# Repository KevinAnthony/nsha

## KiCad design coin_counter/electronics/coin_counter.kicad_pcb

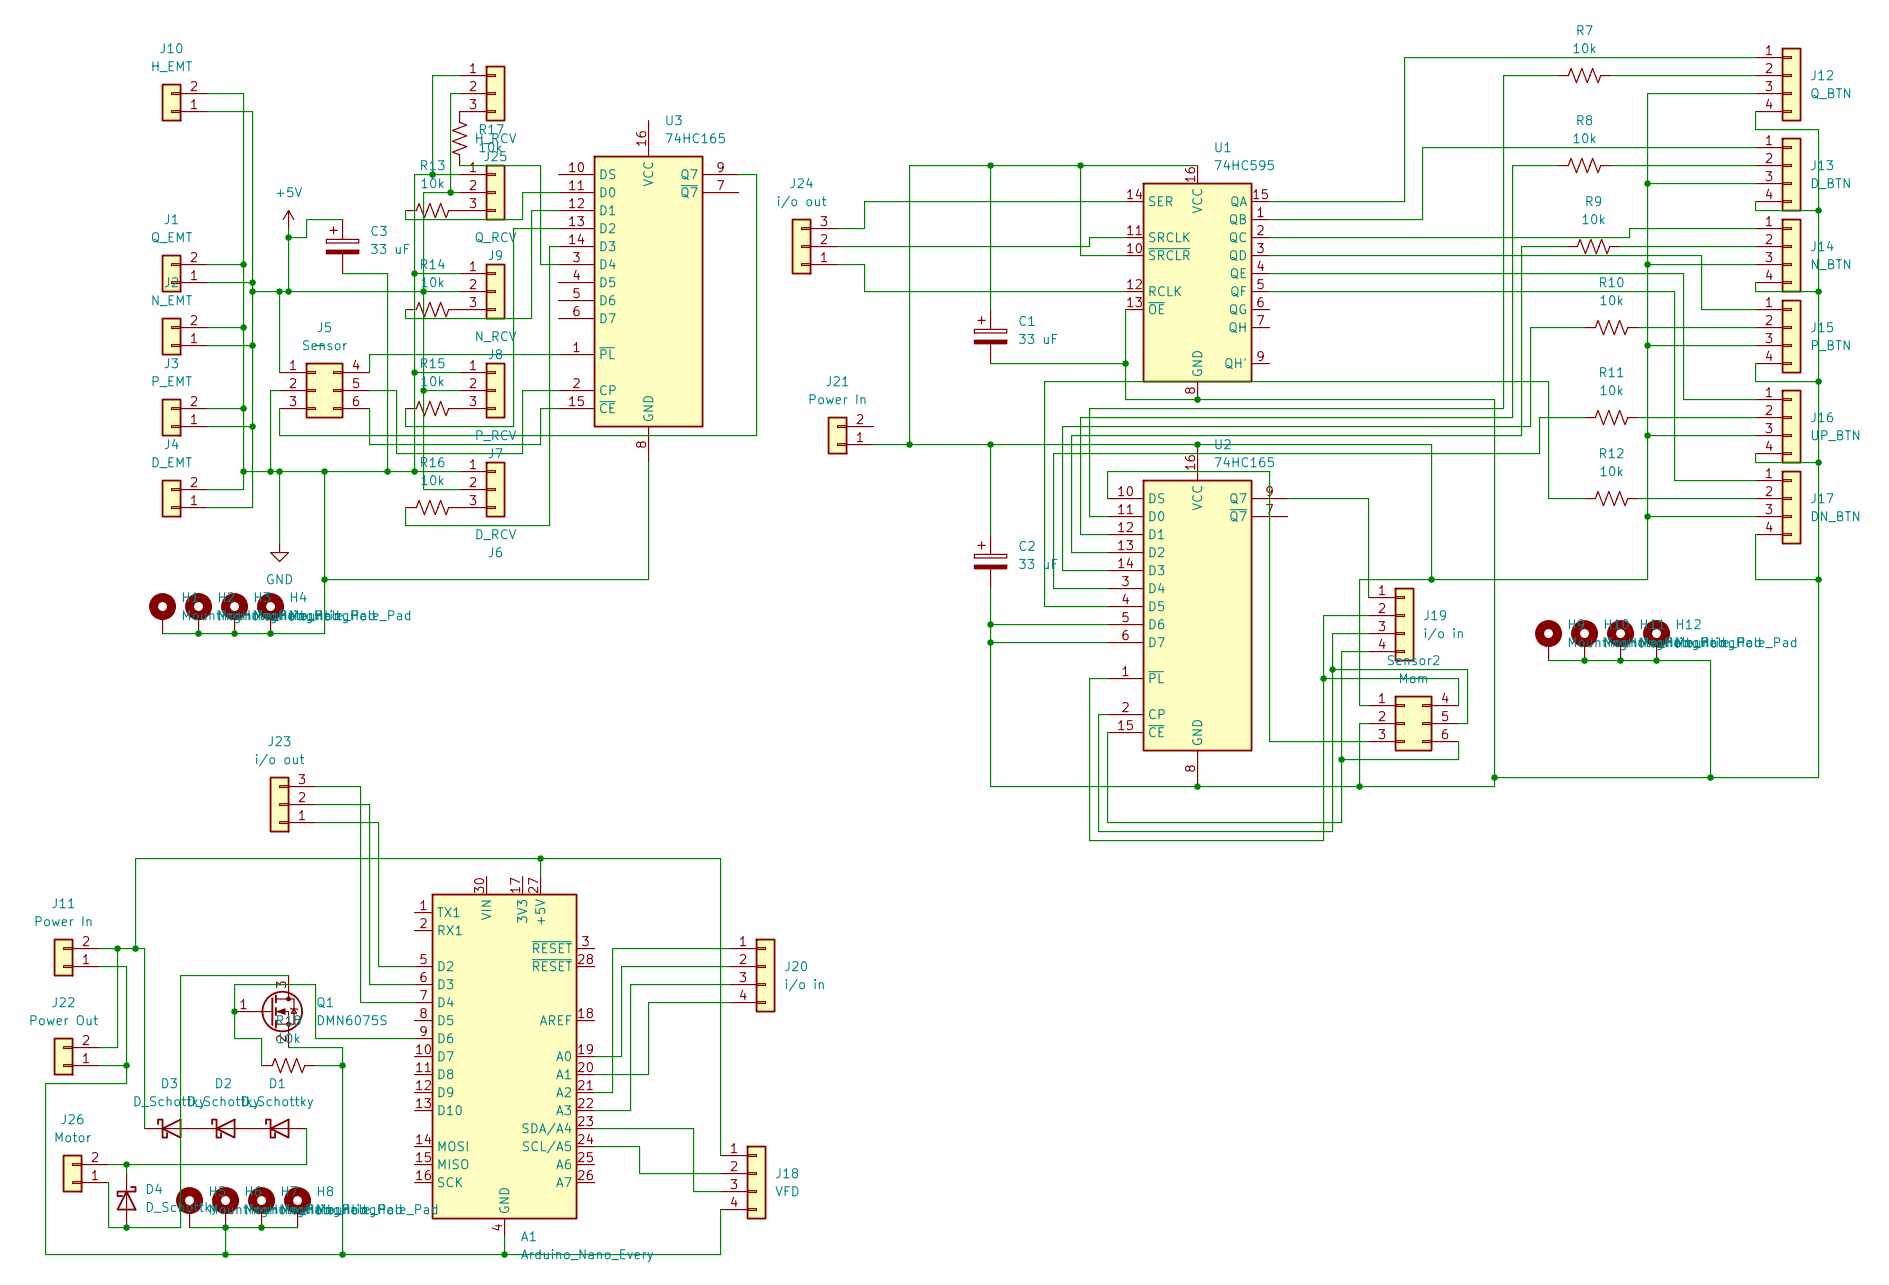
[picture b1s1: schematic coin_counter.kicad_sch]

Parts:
A1: Arduino_Nano_Every; Arduino_Nano
C1, C2, C3: 33 uF; CP_Elec_5x5.9
D1, D2, D3, D4: D_Schottky; D_SMA_Handsoldering
H1, H2, H3, H4, H5, H6, H7, H8, H9, H10, H11, H12: MountingHole_Pad; MountingHole_3.2mm_M3_Pad_Via
J1: Q_EMT; JST_XH_B2B-XH-A_1x02_P2.50mm_Vertical
J2: N_EMT; JST_XH_B2B-XH-A_1x02_P2.50mm_Vertical
J3: P_EMT; JST_XH_B2B-XH-A_1x02_P2.50mm_Vertical
J4: D_EMT; JST_XH_B2B-XH-A_1x02_P2.50mm_Vertical
J5: Sensor; JST_XH_B6B-XH-A_1x06_P2.50mm_Vertical
J6: D_RCV; JST_XH_B3B-XH-A_1x03_P2.50mm_Vertical
J7: P_RCV; JST_XH_B3B-XH-A_1x03_P2.50mm_Vertical
J8: N_RCV; JST_XH_B3B-XH-A_1x03_P2.50mm_Vertical
J9: Q_RCV; JST_XH_B3B-XH-A_1x03_P2.50mm_Vertical
J10: H_EMT; JST_XH_B2B-XH-A_1x02_P2.50mm_Vertical
J11, J21: Power In; JST_XH_B2B-XH-A_1x02_P2.50mm_Vertical
J12: Q_BTN; JST_XH_B4B-XH-A_1x04_P2.50mm_Vertical
J13: D_BTN; JST_XH_B4B-XH-A_1x04_P2.50mm_Vertical
J14: N_BTN; JST_XH_B4B-XH-A_1x04_P2.50mm_Vertical
J15: P_BTN; JST_XH_B4B-XH-A_1x04_P2.50mm_Vertical
J16: UP_BTN; JST_XH_B4B-XH-A_1x04_P2.50mm_Vertical
J17: DN_BTN; JST_XH_B4B-XH-A_1x04_P2.50mm_Vertical
J18: VFD; JST_XH_B4B-XH-A_1x04_P2.50mm_Vertical
J19, J20: i/o in; JST_XH_B4B-XH-A_1x04_P2.50mm_Vertical
J22: Power Out; JST_XH_B2B-XH-A_1x02_P2.50mm_Vertical
J23, J24: i/o out; JST_XH_B3B-XH-A_1x03_P2.50mm_Vertical
J25: H_RCV; JST_XH_B3B-XH-A_1x03_P2.50mm_Vertical
J26: Motor; JST_XH_B2B-XH-A_1x02_P2.50mm_Vertical
Q1: DMN6075S; SOT-23
R7, R8, R9, R10, R11, R12, R13, R14, R15, R16, R17, R18: 10k; R_0201_0603Metric
Sensor2: Mom; JST_XH_B6B-XH-A_1x06_P2.50mm_Vertical
U1: 74HC595; SO-16_3.9x9.9mm_P1.27mm
U2, U3: 74HC165; SO-16_3.9x9.9mm_P1.27mm

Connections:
+5V: C3.1, J1.1, J2.1, J3.1, J4.1, J5.1, J6.2, J7.2, J8.2, J9.2, J10.1, J25.2
GND: C3.2, H1.1, H2.1, H3.1, H4.1, J1.2, J2.2, J3.2, J4.2, J5.2, J6.1, J7.1, J8.1, J9.1, J10.2, J25.1, U3.8 (GND)
unnamed: A1.27 (+5V), D3.1 (K), J11.2, J18.1, J22.2
unnamed: A1.19 (A0), J20.2
unnamed: A1.20 (A1), J20.4
unnamed: A1.21 (A2), J20.1
unnamed: A1.22 (A3), J20.3
unnamed: A1.5 (D2), J23.1
unnamed: A1.6 (D3), J23.2
unnamed: A1.7 (D4), J23.3
unnamed: A1.9 (D6), Q1.1 (G), R18.1
unnamed: A1.24 (SCL/A5), J18.2
unnamed: A1.23 (SDA/A4), J18.3
unnamed: D1.2 (A), D4.1 (K), J26.2
unnamed: D1.1 (K), D2.2 (A)
unnamed: D2.1 (K), D3.2 (A)
unnamed: D4.2 (A), J26.1, Q1.3 (D)
unnamed: J5.3, U3.9 (Q7)
unnamed: J5.4, U3.1 (~PL)
unnamed: J5.5, U3.2 (CP)
unnamed: J5.6, U3.15 (~CE)
unnamed: J6.3, R16.2
unnamed: J7.3, R15.2
unnamed: J8.3, R14.2
unnamed: J9.3, R13.2
unnamed: A1.4 (GND), A1.29 (GND), H5.1, H6.1, H7.1, H8.1, J11.1, J18.4, J22.1, Q1.2 (S), R18.2
unnamed: J12.1, U1.15 (QA)
unnamed: J12.2, R7.2
unnamed: J13.1, U1.1 (QB)
unnamed: J13.2, R8.2
unnamed: J14.1, U1.2 (QC)
unnamed: J14.2, R9.2
unnamed: J15.1, U1.3 (QD)
unnamed: J15.2, R10.2
unnamed: J16.1, U1.4 (QE)
unnamed: J16.2, R11.2
unnamed: J17.1, U1.5 (QF)
unnamed: J17.2, R12.2
unnamed: J19.1, U2.9 (Q7)
unnamed: J19.2, Sensor2.4, U2.1 (~PL)
unnamed: J19.3, Sensor2.5, U2.2 (CP)
unnamed: J19.4, Sensor2.6, U2.15 (~CE)
unnamed: J24.1, U1.12 (RCLK)
unnamed: J24.2, U1.11 (SRCLK)
unnamed: J24.3, U1.14 (SER)
unnamed: J25.3, R17.2
unnamed: Sensor2.3, U2.10 (DS)
unnamed: R7.1, U2.11 (D0)
unnamed: R8.1, U2.12 (D1)
unnamed: R9.1, U2.13 (D2)
unnamed: R10.1, U2.14 (D3)
unnamed: R11.1, U2.3 (D4)
unnamed: R12.1, U2.4 (D5)
unnamed: R13.1, U3.11 (D0)
unnamed: R14.1, U3.12 (D1)
unnamed: R15.1, U3.13 (D2)
unnamed: R16.1, U3.14 (D3)
unnamed: R17.1, U3.3 (D4)

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
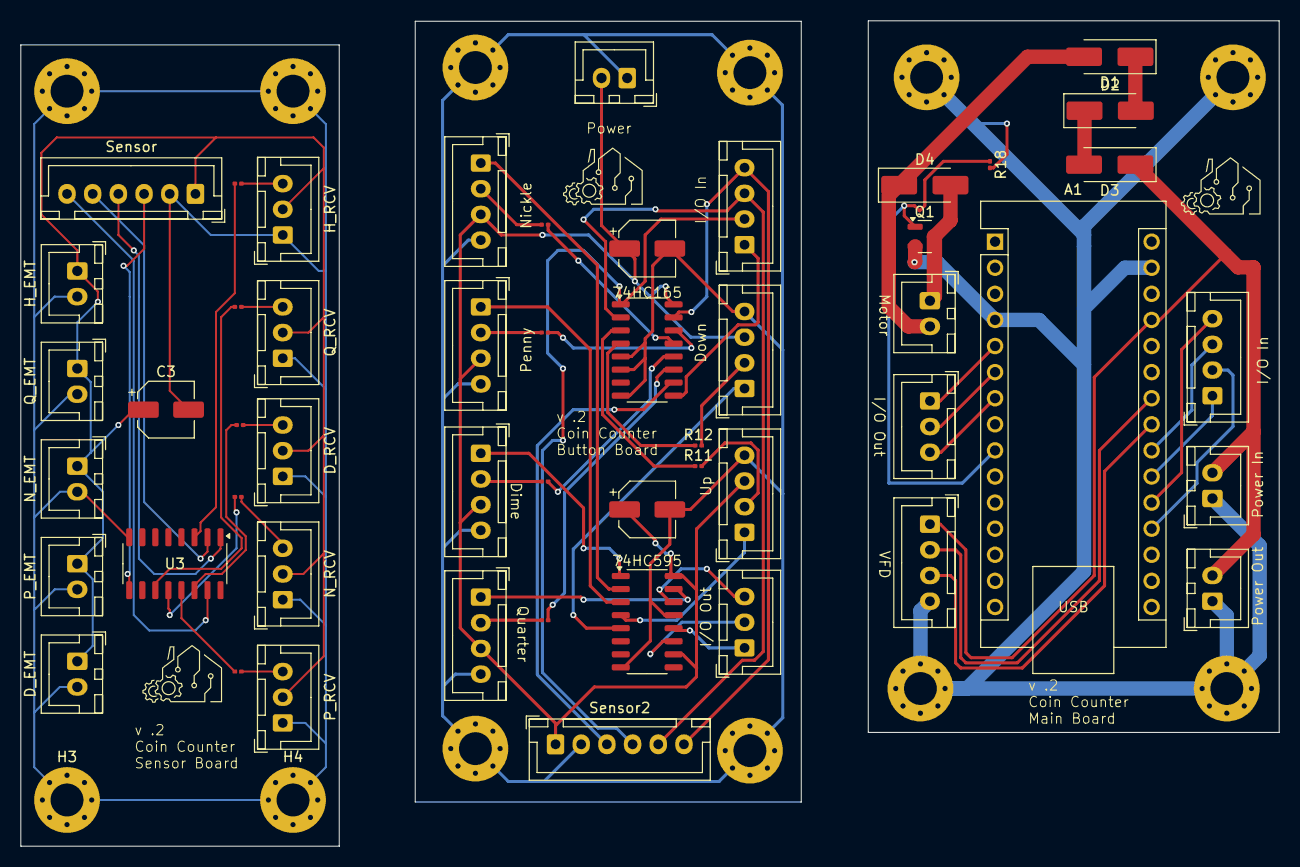
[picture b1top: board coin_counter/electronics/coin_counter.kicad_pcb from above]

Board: 2 copper layers, 122.5 x 80.3 mm, 66 parts (0 on the bottom side), 60 nets.

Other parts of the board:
Button: Board
Main: Board
Sensor_2: Board

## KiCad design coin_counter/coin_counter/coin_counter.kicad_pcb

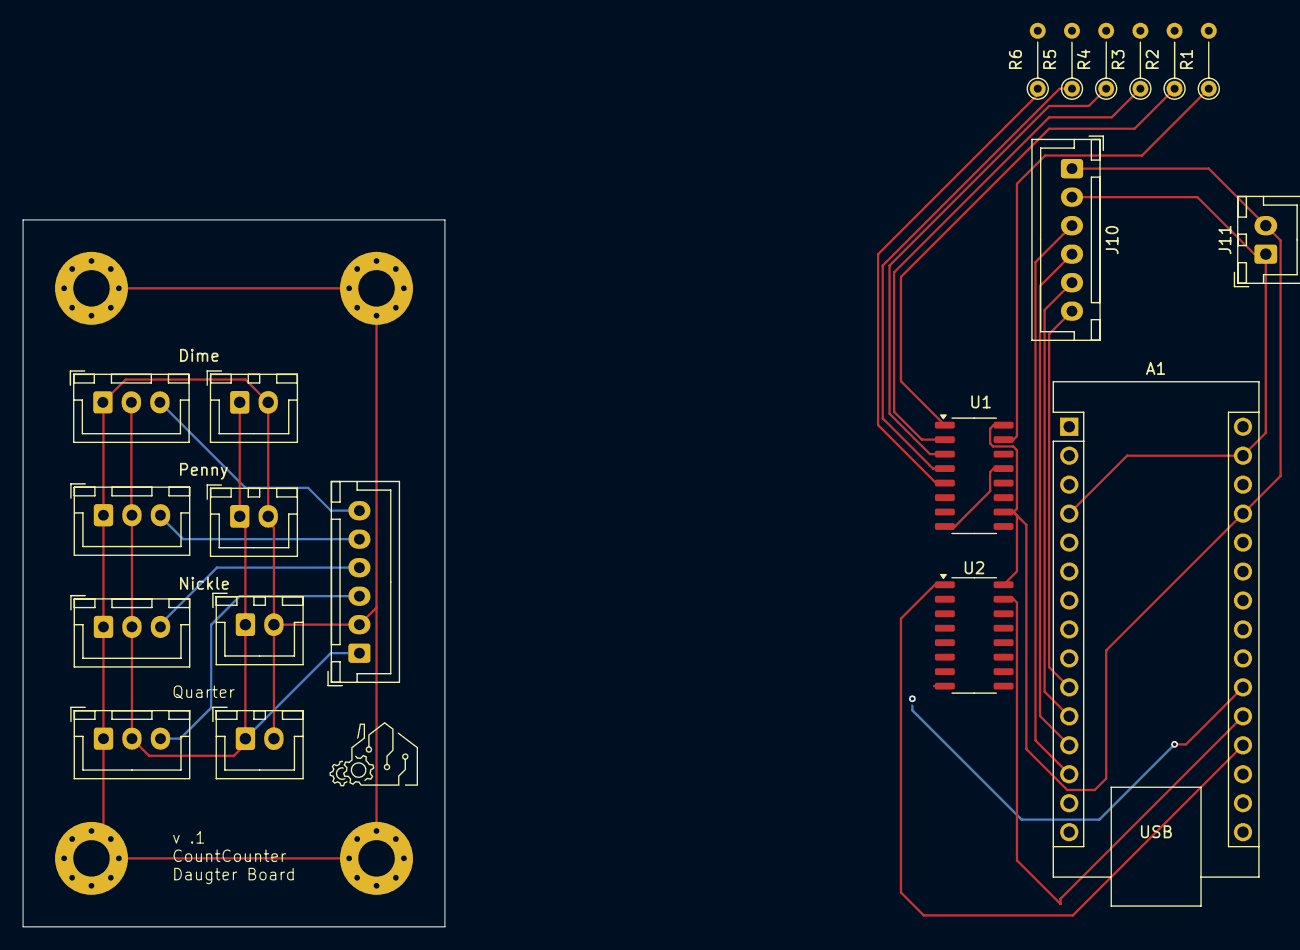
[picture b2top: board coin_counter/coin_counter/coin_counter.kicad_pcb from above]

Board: 2 copper layers, 37.0 x 62.0 mm, 24 parts (0 on the bottom side), 25 nets.

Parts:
A1: Arduino_Nano_Every; Arduino_Nano
H1, H2, H3, H4: MountingHole_Pad; MountingHole_3.2mm_M3_Pad_Via
J1: Q_EMT; JST_XH_B2B-XH-A_1x02_P2.50mm_Vertical
J2: N_EMT; JST_XH_B2B-XH-A_1x02_P2.50mm_Vertical
J3: P_EMT; JST_XH_B2B-XH-A_1x02_P2.50mm_Vertical
J4: D_EMT; JST_XH_B2B-XH-A_1x02_P2.50mm_Vertical
J5, J10: Mom; JST_XH_B6B-XH-A_1x06_P2.50mm_Vertical
J6: D_RCV; JST_XH_B3B-XH-A_1x03_P2.50mm_Vertical
J7: P_RCV; JST_XH_B3B-XH-A_1x03_P2.50mm_Vertical
J8: N_RCV; JST_XH_B3B-XH-A_1x03_P2.50mm_Vertical
J9: Q_RCV; JST_XH_B3B-XH-A_1x03_P2.50mm_Vertical
J11: Power; JST_XH_B2B-XH-A_1x02_P2.50mm_Vertical
R1, R2, R3, R4, R5, R6: 220 Ohm; R_Axial_DIN0204_L3.6mm_D1.6mm_P5.08mm_Vertical
U1: 74HC595; SO-16_3.9x9.9mm_P1.27mm
U2: 74HC165; SO-16_3.9x9.9mm_P1.27mm

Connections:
+5V: J1.1, J2.1, J3.1, J4.1, J5.1, J6.2, J7.2, J8.2, J9.2
GND: H1.1, H2.1, H3.1, H4.1, J1.2, J2.2, J3.2, J4.2, J5.2, J6.1, J7.1, J8.1, J9.1
unnamed: A1.27 (+5V), J10.1, J11.2, U1.10 (~SRCLR), U1.16 (VCC), U2.16 (VCC)
unnamed: A1.19 (A0), U2.1 (~PL)
unnamed: A1.20 (A1), U2.15 (~CE)
unnamed: A1.21 (A2), U2.7 (~Q7)
unnamed: A1.22 (A3), U2.2 (CP)
unnamed: A1.5 (D2), U1.12 (RCLK)
unnamed: A1.6 (D3), U1.11 (SRCLK)
unnamed: A1.7 (D4), U1.14 (SER)
unnamed: A1.10 (D7), J10.6
unnamed: A1.11 (D8), J10.5
unnamed: A1.12 (D9), J10.4
unnamed: A1.13 (D10), J10.3
unnamed: J5.3, J9.3
unnamed: J5.4, J8.3
unnamed: J5.5, J7.3
unnamed: J5.6, J6.3
unnamed: A1.4 (GND), A1.29 (GND), J10.2, J11.1, U1.8 (GND), U1.13 (~OE), U2.8 (GND)
unnamed: R1.1, U1.15 (QA)
unnamed: R2.1, U1.1 (QB)
unnamed: R3.1, U1.2 (QC)
unnamed: R4.1, U1.3 (QD)
unnamed: R5.1, U1.4 (QE)
unnamed: R6.1, U1.5 (QF)

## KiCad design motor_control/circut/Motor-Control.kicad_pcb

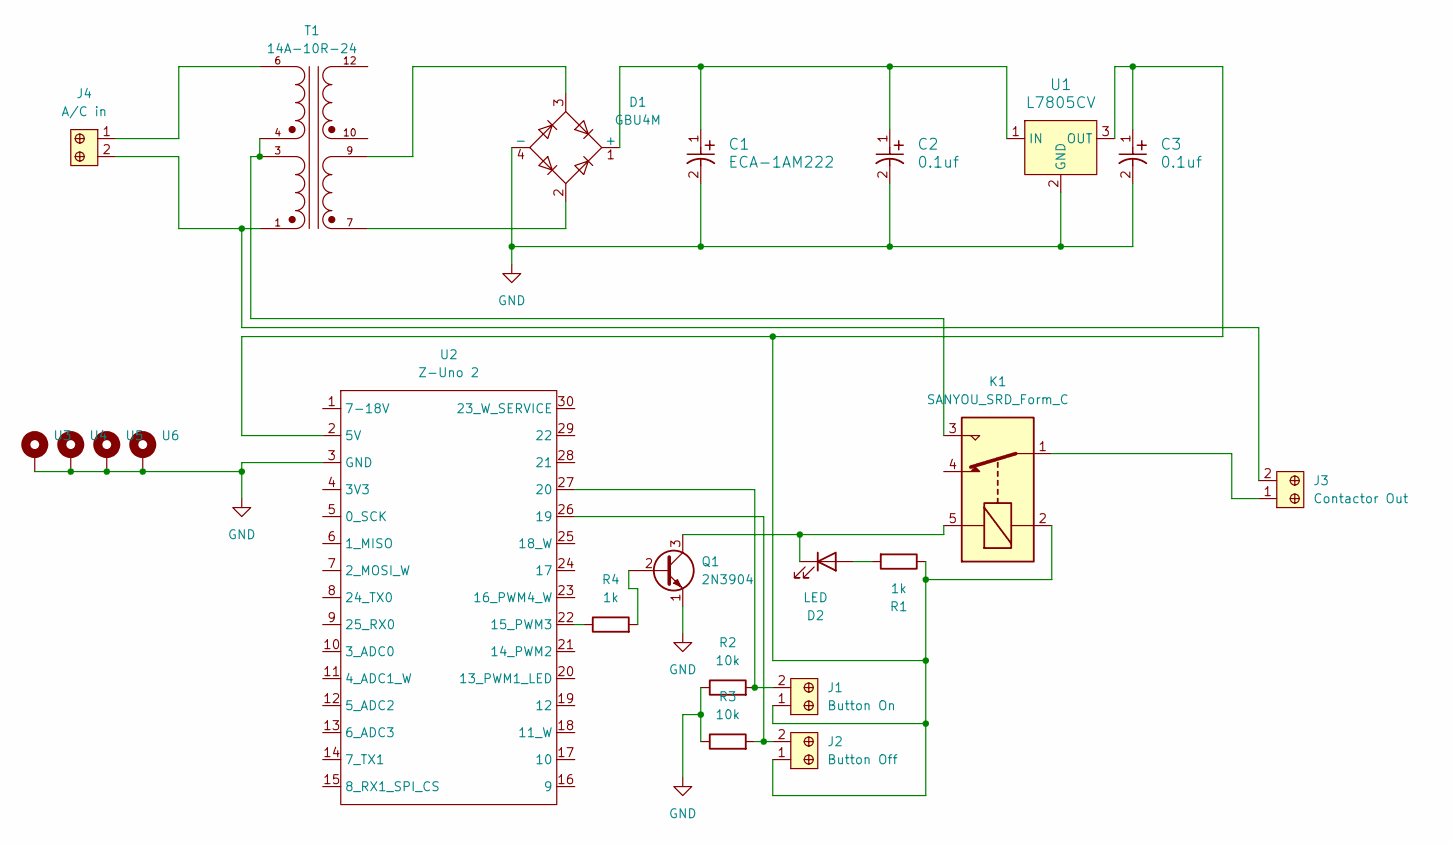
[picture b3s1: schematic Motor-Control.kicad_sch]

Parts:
C1: ECA-1AM222; PCAP_10x20_PAN
C2, C3: 0.1uf; CAP_C322_KEM
D1: GBU4M; Diode_Bridge_Vishay_GBU
D2: LED; LED_D3.0mm
J1: Button On; Terminal_Block_D1.3mm_P5mm; MPN 1935161; Digi-Key_PN 277-1667-ND
J2: Button Off; Terminal_Block_D1.3mm_P5mm; MPN 1935161; Digi-Key_PN 277-1667-ND
J3: Contactor Out; Terminal_Block_D1.3mm_P5mm; MPN 1935161; Digi-Key_PN 277-1667-ND
J4: A/C in; Terminal_Block_D1.3mm_P5mm; MPN 1935161; Digi-Key_PN 277-1667-ND
K1: SANYOU_SRD_Form_C; Relay_SPDT_SANYOU_SRD_Series_Form_C
Q1: 2N3904; TO-92_Inline
R1, R4: 1k; R_Axial_DIN0414_L11.9mm_D4.5mm_P20.32mm_Horizontal
R2, R3: 10k; R_Axial_DIN0414_L11.9mm_D4.5mm_P20.32mm_Horizontal
T1: 14A-10R-24; XFMR_14A-10R-24; PARTREV 12.19
U1: L7805CV; TO-220-3; MPN L7805CV; Digi-Key_PN 497-1443-5-ND
U2: Z-Uno 2; DIP-30_W17.78mm
U3, U4, U5, U6: MountingHole_3.2mm_M3_ISO7380_Pad_TopBottom

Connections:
GND: C1.2, C2.2, C3.2, D1.4 (-), Q1.1 (E), R2.1, R3.1, U1.2 (GND), U2.3 (GND), U3.1, U4.1, U5.1, U6.1
unnamed: C1.1, C2.1, D1.1 (+), U1.1 (IN)
unnamed: D1.2, T1.7
unnamed: D1.3, T1.9
unnamed: D2.2 (A), R1.2
unnamed: D2.1 (K), K1.5, Q1.3 (C)
unnamed: J3.1, K1.1
unnamed: J3.2, J4.2, T1.1
unnamed: J4.1, T1.6
unnamed: K1.3, T1.3, T1.4
unnamed: Q1.2 (B), R4.2
unnamed: C3.1, J1.1, J2.1, K1.2, R1.1, U1.3 (OUT), U2.2 (5V)
unnamed: R4.1, U2.22 (15_PWM3)
unnamed: J2.2, R3.2, U2.26 (19)
unnamed: J1.2, R2.2, U2.27 (20)

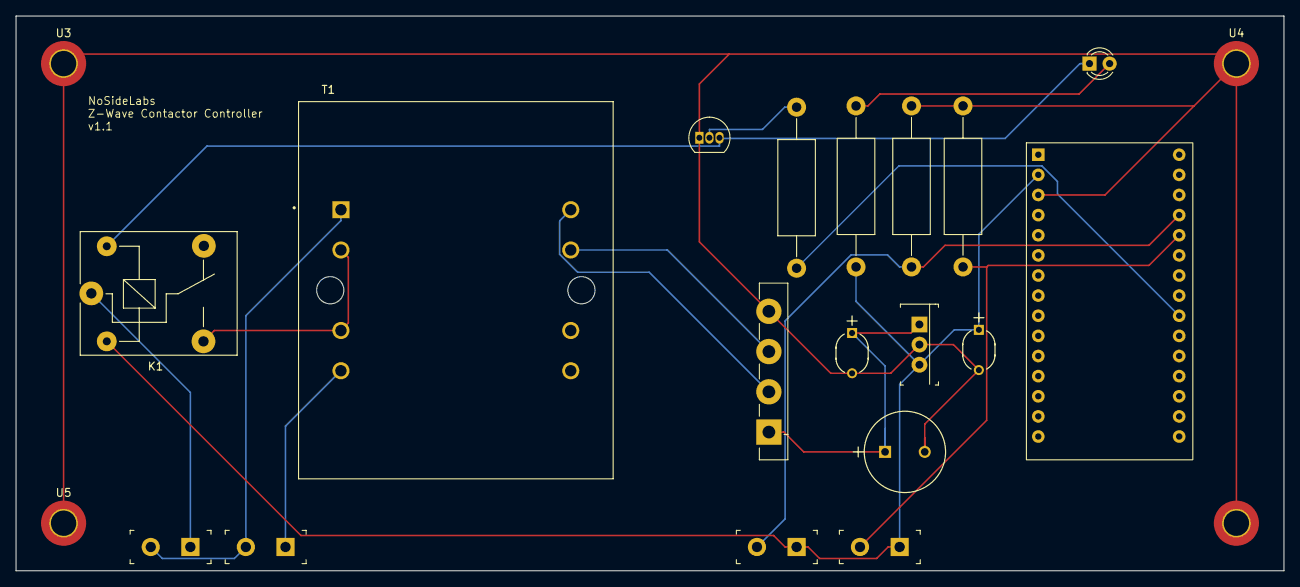
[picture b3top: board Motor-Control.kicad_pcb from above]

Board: 2 copper layers, 160.0 x 70.0 mm, 22 parts (0 on the bottom side), 15 nets.

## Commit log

2024-11-03 motor-starter-v1
2024-11-03 skip zwave QR codes
2025-02-23 remove zuno folder
2025-02-23 Initial Daughter board design
2025-02-25 more
2025-03-07 coin cointer v2
2025-03-07 checkin
2025-03-07 shift
2025-03-09 shift inputs doneish
2025-03-09 git ignore
2025-03-10 masking and update class
2025-03-10 fixed errors
2025-03-10 formatting and moving code
2025-03-10 more work, mosfets and diodes
2025-03-11 board layouts button and main
2025-03-11 remove autosave
2025-03-11 add rule checker
2025-03-11 v2 of boards
2025-03-14 add some functions to coin
2025-03-16 only take the VFD stuff I need
